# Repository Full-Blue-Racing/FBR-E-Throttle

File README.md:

# Wiring

# APPS

5V input/output. Use a voltage divider/other approach to condition the analogue output to a range that can be read by ESP32

# TPS

# Nema 23 Stepper motor

https://www.motechmotor.com/productDetail-0105-81.html

step angle $1.8\degree$

# TMC5160 driver board

datasheet: [TMC5160 Datasheet (long))](https://www.analog.com/media/en/technical-documentation/data-sheets/TMC5160A_datasheet_rev1.18.pdf)

Description: [TMC5160 BOB Description](https://www.analog.com/media/en/technical-documentation/data-sheets/tmc5160-bob_datasheet_rev1.10.pdf)

Install this library developed by tommag. both `TMC5160.h` and `Bitfield.h` are included

https://github.com/tommag/TMC5160_Arduino

# Motor torque

Adjust motor torque by writing to these registers (in setup, after SPI communication and motor has been initialised):

```
  motor.writeRegister(TMC5160_Reg::GLOBAL_SCALER, 200); //32-255
  motor.writeRegister(TMC5160_Reg::IHOLD_IRUN, 0x00011F14);
```

The complete list of register can be found in /TMC5160_registers.h

The `IHOLD_IRUN` register format:

* Bits 0-4: ihold (in this case hex(14) = dec(20))(0-31) (set to <= 70% of irun)
* Bits 8-12: irun (0-31)
* Bits 16-19: iholddelay

! For some reasons changing motorParams didn't work for me. had to write to register for the change to stick

## Resources

- [PID Controller in C](https://deepbluembedded.com/esp32-timers-timer-interrupt-tutorial-arduino-ide/)
- [ESP32 Arduino IDE Timer Interrupts Reference](https://deepbluembedded.com/esp32-timers-timer-interrupt-tutorial-arduino-ide/)

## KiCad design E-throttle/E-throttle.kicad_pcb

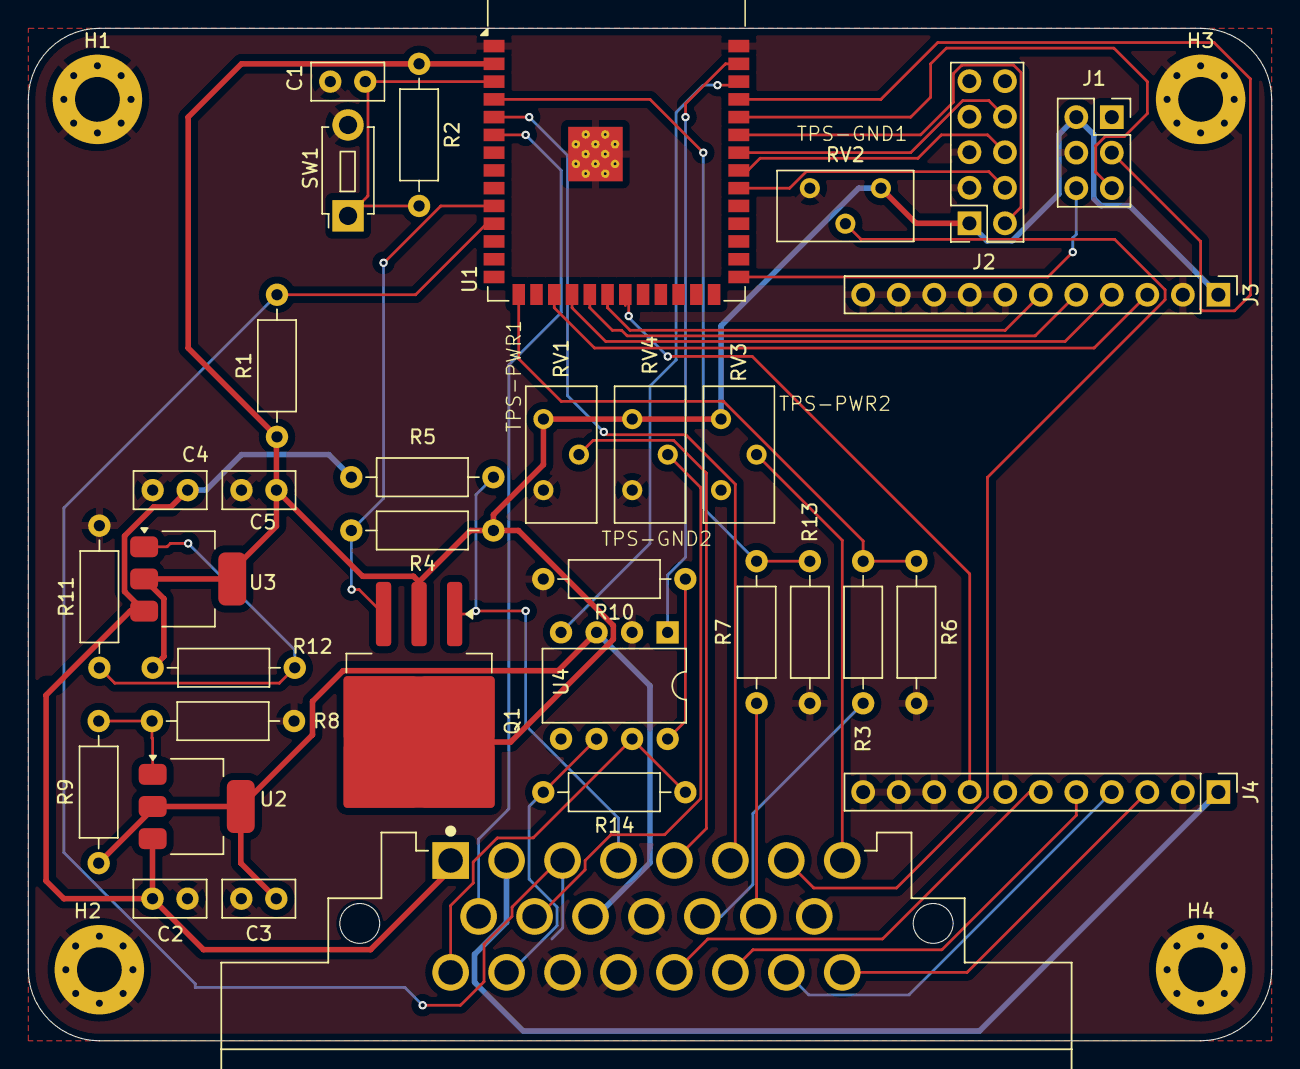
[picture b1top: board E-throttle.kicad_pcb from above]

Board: 2 copper layers, 88.9 x 72.4 mm, 38 parts (0 on the bottom side), 42 nets.

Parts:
C1, C3, C5: 1u; C_Disc_D5.0mm_W2.5mm_P2.50mm
C2, C4: 0.1u; C_Disc_D5.0mm_W2.5mm_P2.50mm
H1, H2, H3, H4: MountingHole_Pad; MountingHole_3.2mm_M3_Pad_Via
J1: PROG; PinSocket_2x03_P2.54mm_Vertical
J2: JTAG; PinSocket_2x05_P2.54mm_Vertical
J3, J4: Conn_01x11; PinHeader_1x11_P2.54mm_Vertical
J5: 776087-1; TE_776087-1
Q1: NMOS; TO-263-3_TabPin2
R1: 100k; R_Axial_DIN0207_L6.3mm_D2.5mm_P10.16mm_Horizontal
R2: 10k; R_Axial_DIN0207_L6.3mm_D2.5mm_P10.16mm_Horizontal
R3, R7: 33.2k; R_Axial_DIN0207_L6.3mm_D2.5mm_P10.16mm_Horizontal
R4, R5: R_Small; R_Axial_DIN0207_L6.3mm_D2.5mm_P10.16mm_Horizontal
R6, R13: 66.5k; R_Axial_DIN0207_L6.3mm_D2.5mm_P10.16mm_Horizontal
R8: 715; R_Axial_DIN0207_L6.3mm_D2.5mm_P10.16mm_Horizontal
R9, R12: 240; R_Axial_DIN0207_L6.3mm_D2.5mm_P10.16mm_Horizontal
R10: 20k; R_Axial_DIN0207_L6.3mm_D2.5mm_P10.16mm_Horizontal
R11: 392; R_Axial_DIN0207_L6.3mm_D2.5mm_P10.16mm_Horizontal
R14: 120; R_Axial_DIN0207_L6.3mm_D2.5mm_P10.16mm_Horizontal
RV1, RV2, RV3, RV4: 100k; Potentiometer_Bourns_3296Y_Vertical
SW1: SW_Push; SW_PUSH_1P1T_6x3.5mm_H4.3_APEM_MJTP1243
U1: ESP32-S3-WROOM-1-N16R8; ESP32-S3-WROOM-1
U2, U3: LM317_SOT-223; SOT-223-3_TabPin2
U4: MCP2551-I-P; DIP-8_W7.62mm

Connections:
+3V3: C5.1, J1.2, J2.1, J3.1, Q1.2 (G), R1.1, R2.1, R4.1, R12.1, RV1.1, RV2.1, RV3.1, RV4.1, U1.2 (3V3), U3.2 (VO)
+5V: C3.1, J5.11, R9.1, U2.2 (VO), U4.3 (VDD)
+12V: C2.1, C4.1, J5.1, R5.1, U2.3 (VI), U3.3 (VI)
+12VStep: J4.1, J5.2
/APPS-SIG1: J5.13, R3.1
/APPS-SIG1-OUT: R3.2, R6.1, U1.15 (IO3)
/APPS-SIG2: J5.14, R7.1
/APPS-SIG2-OUT: R7.2, R13.1, U1.4 (IO4)
/BLIP-IN: J5.4, Q1.1 (D), R5.2
/BLIP-OUT: Q1.3 (S), R4.2, U1.10 (IO17)
/BOOTOPT: J1.6, U1.27 (IO0)
/CAN-H: J5.16, R14.1, U4.7 (CANH)
/CAN-L: J5.17, R14.2, U4.6 (CANL)
/CAN_RX: U1.38 (IO2), U4.4 (RXD)
/CAN_TX: U1.39 (IO1), U4.1 (TXD)
/DIAG0: J4.8, U1.21 (IO13)
/ENABLE: C1.1, R2.2, SW1.1, U1.3 (EN)
/IDLE: J5.3, R1.2, U1.11 (IO18)
/JTAG_TCK: J2.4, U1.32 (IO39)
/JTAG_TDI: J2.8, U1.34 (IO41)
/JTAG_TDO: J2.6, U1.33 (IO40)
/JTAG_TMS: J2.2, U1.35 (IO42)
/SPI-CS: J3.3, U1.17 (IO9)
/SPI-MISO: J3.6, U1.20 (IO12)
/SPI-MOSI: J3.5, U1.19 (IO11)
/SPI-SCK: J3.4, U1.18 (IO10)
/STEP-1+: J4.6, J5.20
/STEP-1-: J4.5, J5.21
/STEP-2+: J4.4, J5.22
/STEP-2-: J4.3, J5.23
/TPS-GND1: J5.7, RV2.2
/TPS-GND2: J5.10, RV4.2
/TPS-PWR1: J5.5, RV1.2
/TPS-PWR2: J5.8, RV3.2
/TPS-SIG1: J5.6, U1.5 (IO5)
/TPS-SIG2: J5.9, U1.6 (IO6)
/UART_RX: J1.5, U1.36 (RXD0)
/UART_TX: J1.3, U1.37 (TXD0)
GND: C1.2, C2.2, C3.2, C4.2, C5.2, H1.1, H2.1, H3.1, H4.1, J1.4, J2.3, J2.5, J2.7, J2.9, J3.2, J3.7, J3.8, J3.9, J3.10, J3.11, J4.2, J4.7, J4.9, J4.10, J4.11, J5.12, J5.15, J5.18, J5.19, R6.2, R8.2, R10.2, R11.2, R13.2, RV1.3, RV2.3, RV3.3, RV4.3, SW1.2, U1.1 (GND), U1.40 (GND), U1.41 (GND), U4.2 (VSS)
unnamed: R8.1, R9.2, U2.1 (ADJ)
unnamed: R11.1, R12.2, U3.1 (ADJ)
unnamed: R10.1, U4.8 (Rs)

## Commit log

2025-01-25 Added Stepper Motor Driver (Not Integrated), Deleted CAN Bus Controller MCP2515
    Added Stepper Motor Driver (Not Integrated),
    Deleted CAN Bus Controller MCP2515
2025-02-02 Connector Complete
2025-02-02 Schematic Complete
2025-02-07 Before Feb 7's Session
2025-02-07 Footprint Complete
2025-02-08 Wiring completed
2025-02-18 Completed wiring 2.0
2025-02-18 Add .gitignore
2025-02-18 Untrack gitignored files
2025-02-18 Add logo and attribution to PCB
2026-02-01 Added Simple Program for Analogue Read
2026-02-06 adjusted motor torque, updated documentation
